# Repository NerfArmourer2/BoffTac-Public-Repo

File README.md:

All content is CC0 or Public Domain. These works can be used for any purpose, commerical or otherwise, with the need for permission. I would appreciate attribution where appropriate, however. :)

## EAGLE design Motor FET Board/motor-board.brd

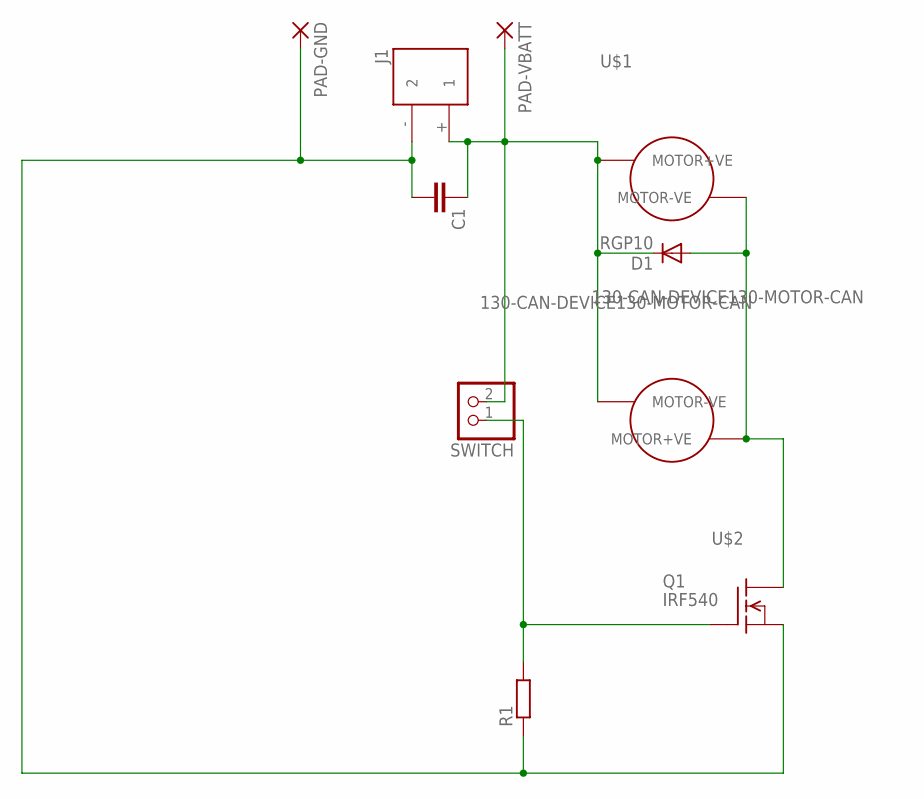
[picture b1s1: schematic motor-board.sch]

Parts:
C1: C-EU050-024X044; C050-024X044
D1: RGP10; DO41-10
J1: XT60_FEMALE
PAD-GND: WIREPAD3,81/1,4; 3,81/1,4
PAD-VBATT: WIREPAD3,81/1,4; 3,81/1,4
Q1: IRF540; TO220
R1: R-EU_0309/10; 0309/10
SWITCH: PINHD-1X2; 1X02
U$1, U$2: 130-CAN-DEVICE130-MOTOR-CAN; 130-MOTOR-CAN

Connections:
GND: C1.2, J1.- (2), PAD-GND.1, Q1.3 (S), R1.1
MOTOR-VE: D1.A, Q1.2 (D), U$1.MOTOR-VE, U$2.MOTOR+VE
unnamed: Q1.1 (G), R1.2, SWITCH.1
VBATT: C1.1, D1.C, J1.+ (1), PAD-VBATT.1, SWITCH.2, U$1.MOTOR+VE, U$2.MOTOR-VE

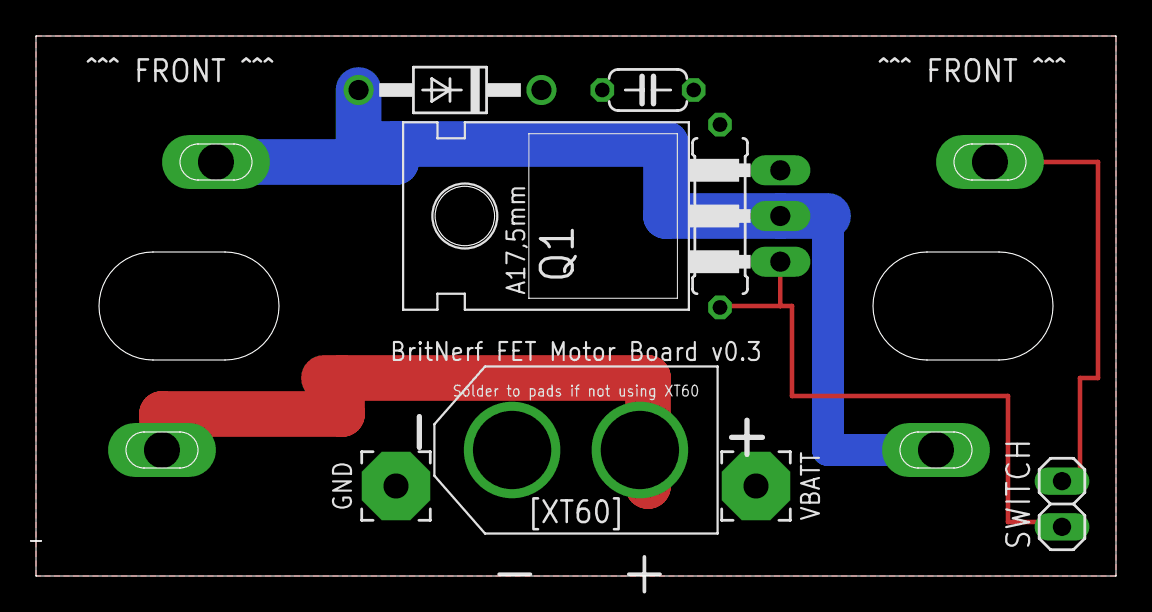
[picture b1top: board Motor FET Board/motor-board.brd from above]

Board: 2 copper layers, 60.0 x 30.0 mm, 10 parts (0 on the bottom side), 4 nets.

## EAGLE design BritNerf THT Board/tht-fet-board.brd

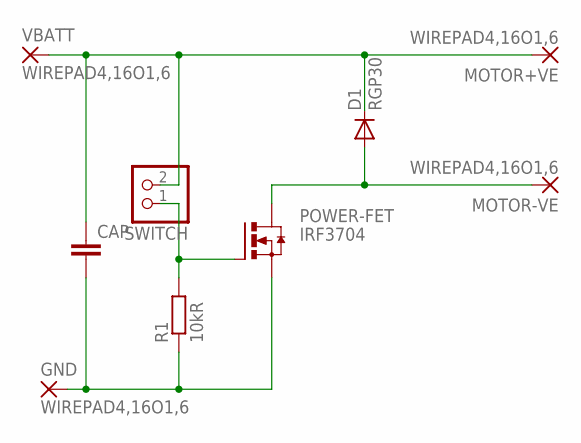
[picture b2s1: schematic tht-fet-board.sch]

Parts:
CAP: C-EU025-024X044; C025-024X044
D1: RGP30; DO201-15
GND: WIREPAD4,16O1,6; 4,16O1,6
MOTOR+VE: WIREPAD4,16O1,6; 4,16O1,6
MOTOR-VE: WIREPAD4,16O1,6; 4,16O1,6
POWER-FET: IRF3704; TO220AH
R1: 10kR; 0207/15
SWITCH: PINHD-1X2; 1X02
VBATT: WIREPAD4,16O1,6; 4,16O1,6

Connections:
GATE: POWER-FET.B (G), R1.2, SWITCH.1
GND: CAP.2, GND.1, POWER-FET.E (S), R1.1
MOTOR-VE: D1.A, MOTOR-VE.1, POWER-FET.C (D)
VBATT: CAP.1, D1.C, MOTOR+VE.1, SWITCH.2, VBATT.1

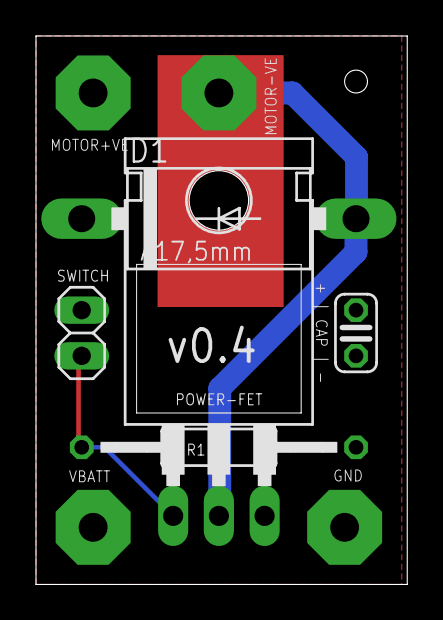
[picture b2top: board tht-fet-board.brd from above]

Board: 2 copper layers, 20.6 x 30.5 mm, 9 parts (0 on the bottom side), 4 nets.

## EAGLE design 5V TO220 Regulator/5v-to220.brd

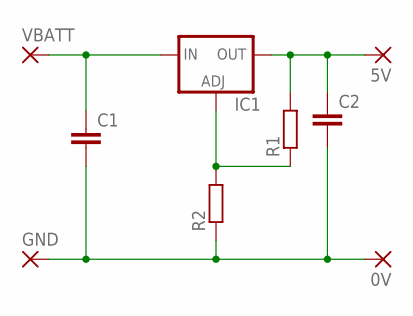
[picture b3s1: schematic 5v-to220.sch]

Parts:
0V, 5V: WIREPAD4,16O1,6; 4,16O1,6
C1, C2: C-EU050-024X044; C050-024X044
GND: WIREPAD4,16O1,6; 4,16O1,6
IC1: LM138-TL; TO220L1
R1, R2: R-EU_0207/10; 0207/10
VBATT: WIREPAD4,16O1,6; 4,16O1,6

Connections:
5V: 5V.1, C2.1, IC1.2 (OUT), R1.2
ADJ: IC1.1 (ADJ), R1.1, R2.2
GND: 0V.1, C1.2, C2.2, GND.1, R2.1
VBATT: C1.1, IC1.3 (IN), VBATT.1

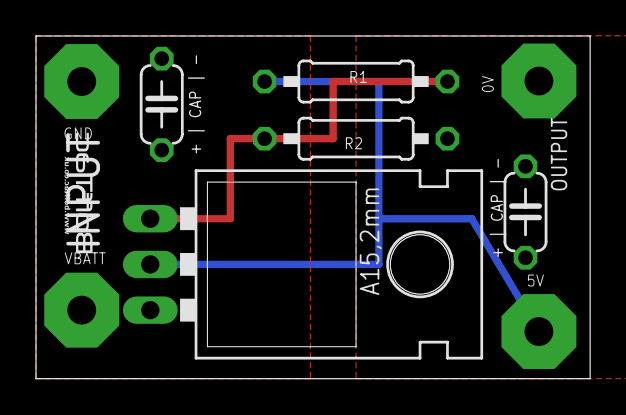
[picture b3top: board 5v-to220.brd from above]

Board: 2 copper layers, 30.8 x 19.0 mm, 9 parts (0 on the bottom side), 4 nets.

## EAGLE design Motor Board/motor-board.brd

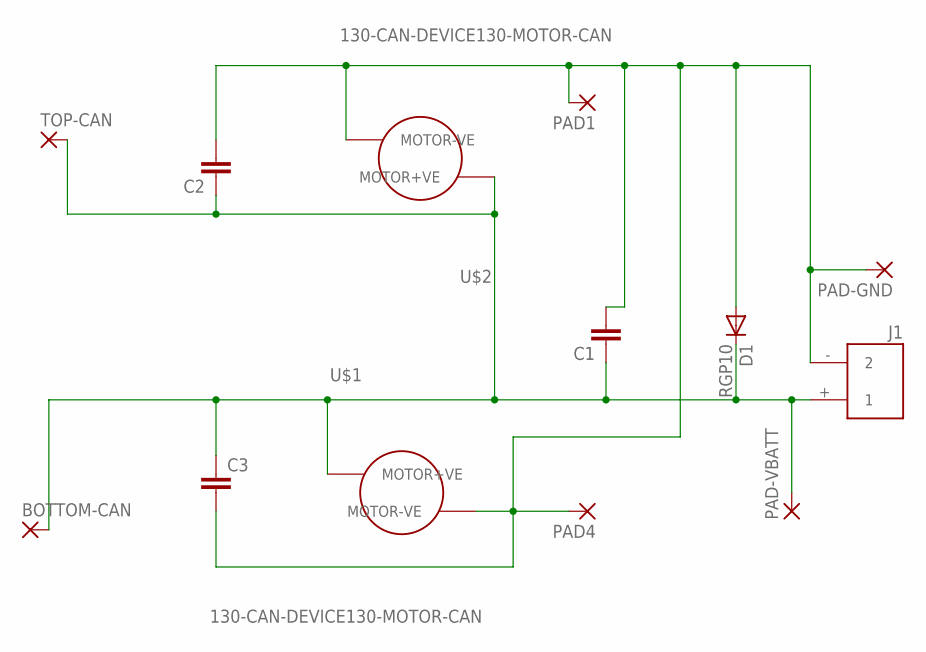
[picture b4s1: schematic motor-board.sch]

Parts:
BOTTOM-CAN: WIREPADSMD1,27-254; SMD1,27-2,54
C1, C2, C3: C-EU050-024X044; C050-024X044
D1: RGP10; DO41-10
J1: XT60_FEMALE
PAD1, PAD4: WIREPADSMD1,27-254; SMD1,27-2,54
PAD-GND: WIREPAD3,81/1,4; 3,81/1,4
PAD-VBATT: WIREPAD3,81/1,4; 3,81/1,4
TOP-CAN: WIREPADSMD1,27-254; SMD1,27-2,54
U$1, U$2: 130-CAN-DEVICE130-MOTOR-CAN; 130-MOTOR-CAN

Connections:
GND: C1.2, C2.2, C3.2, D1.A, J1.- (2), PAD1.1, PAD4.1, PAD-GND.1, U$1.MOTOR-VE, U$2.MOTOR-VE
VBATT: BOTTOM-CAN.1, C1.1, C2.1, C3.1, D1.C, J1.+ (1), PAD-VBATT.1, TOP-CAN.1, U$1.MOTOR+VE, U$2.MOTOR+VE

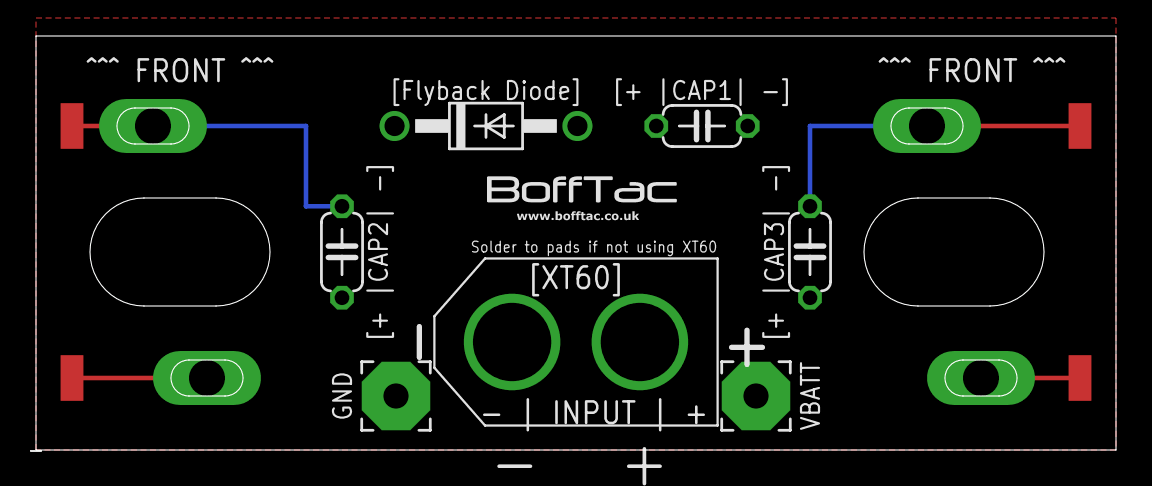
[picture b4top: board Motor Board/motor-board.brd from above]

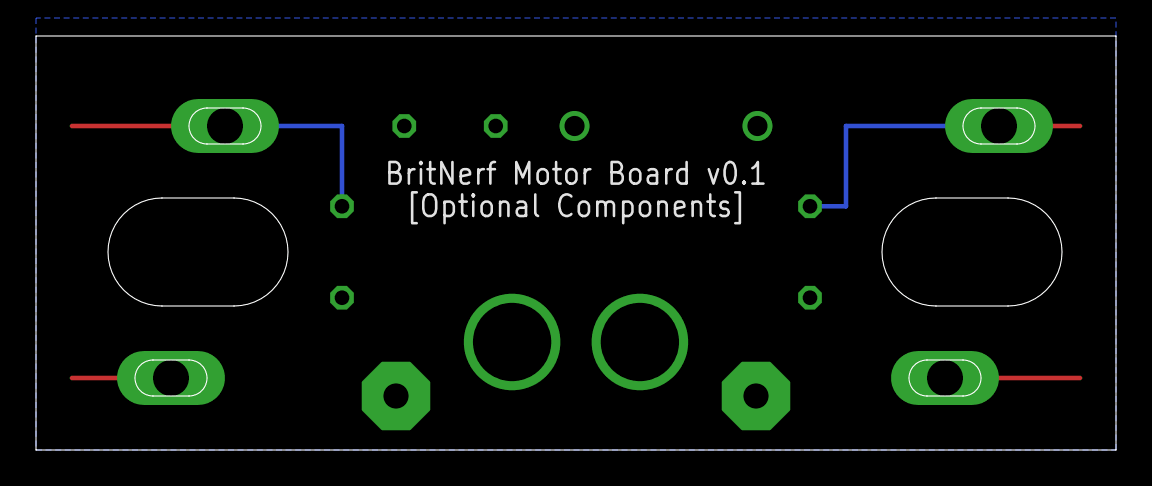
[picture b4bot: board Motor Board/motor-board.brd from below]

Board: 2 copper layers, 60.0 x 23.0 mm, 13 parts (2 on the bottom side), 2 nets.

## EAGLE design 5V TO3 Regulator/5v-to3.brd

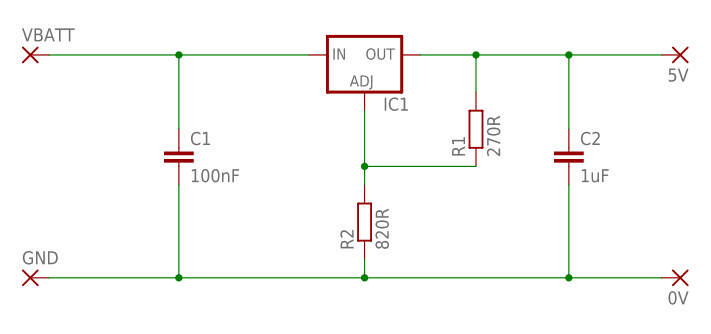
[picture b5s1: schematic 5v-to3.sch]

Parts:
0V, 5V: WIREPAD4,16O1,6; 4,16O1,6
C1: 100nF; C050-024X044
C2: 1uF; C050-024X044
GND: WIREPAD4,16O1,6; 4,16O1,6
IC1: LM138-TO3; TO3-K02
R1: 270R; 0207/7
R2: 820R; 0207/7
VBATT: WIREPAD4,16O1,6; 4,16O1,6

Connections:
5V: 5V.1, C2.1, IC1.3 (OUT), R1.2
ADJ: IC1.2 (ADJ), R1.1, R2.2
GND: 0V.1, C1.2, C2.2, GND.1, R2.1
VBATT: C1.1, IC1.1 (IN), VBATT.1

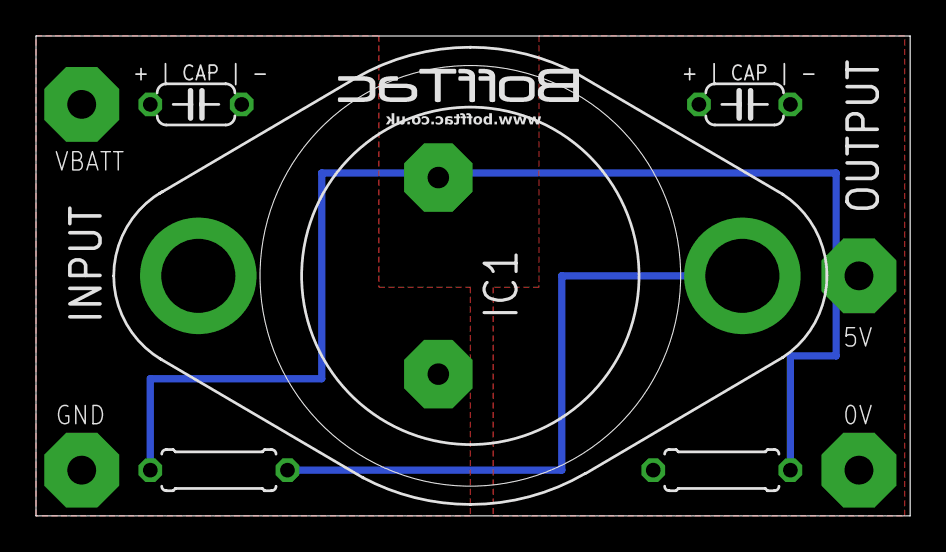
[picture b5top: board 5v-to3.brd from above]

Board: 2 copper layers, 48.6 x 26.7 mm, 9 parts (0 on the bottom side), 4 nets.

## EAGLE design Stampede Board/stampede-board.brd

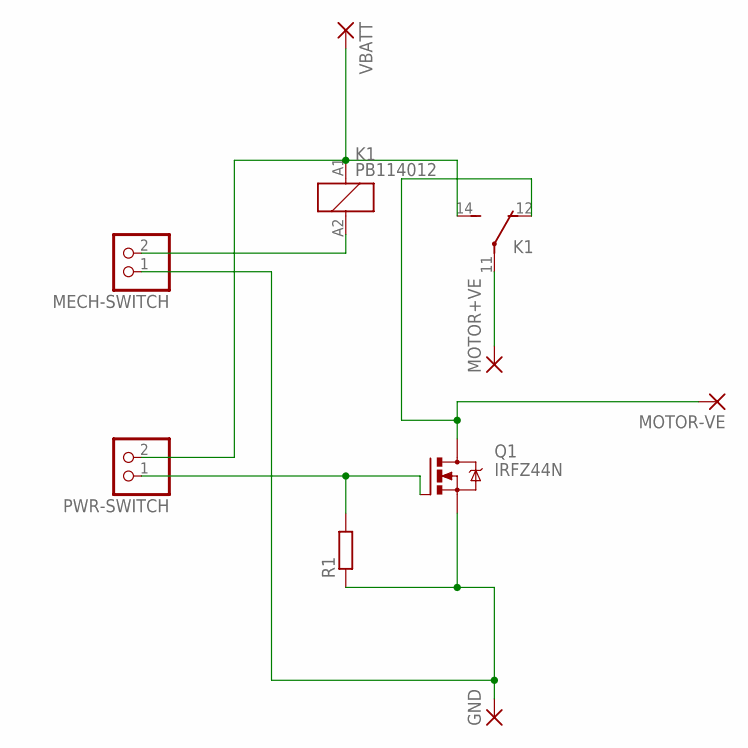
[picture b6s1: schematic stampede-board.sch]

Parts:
GND: WIREPAD3,17/1,3; 3,17/1,3
K1: PB114012; PB
MECH-SWITCH: PINHD-1X2; 1X02
MOTOR+VE: WIREPAD3,17/1,3; 3,17/1,3
MOTOR-VE: WIREPAD3,17/1,3; 3,17/1,3
PWR-SWITCH: PINHD-1X2; 1X02
Q1: IRFZ44N; TO220BV
R1: R-EU_0207/7; 0207/7
VBATT: WIREPAD3,17/1,3; 3,17/1,3

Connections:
GATE: PWR-SWITCH.1, Q1.G, R1.2
GND: GND.1, MECH-SWITCH.1, Q1.S, R1.1
MOTOR+VE: K1.11, MOTOR+VE.1
MOTOR-VE: K1.12 (O), MOTOR-VE.1, Q1.D
unnamed: K1.A2 (2), MECH-SWITCH.2
VBATT: K1.14 (S), K1.A1 (1), PWR-SWITCH.2, VBATT.1

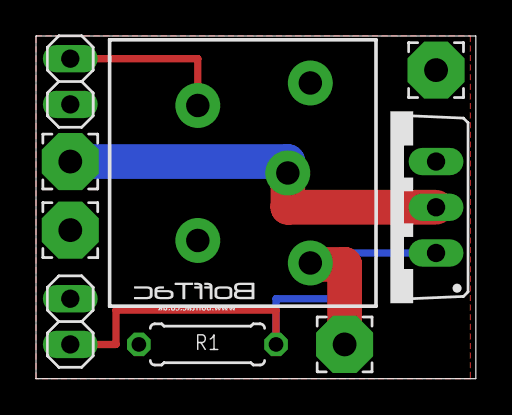
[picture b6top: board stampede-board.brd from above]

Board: 2 copper layers, 24.4 x 19.0 mm, 9 parts (0 on the bottom side), 6 nets.

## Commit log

2019-02-19 Initial commit
    Pushed all the original files to the Repo
2019-02-19 Quality of Life Update
    1: Labelled capacitor polarities on regulator boards
    2: Labelled input and output edges on the same
    3: Ran CAM processor for all changes and added them to a manufacturer friendly .zip file
2019-02-19 Motor Board Push
    Added a PCB mounting board for motors including EMF suppression and optional flyback diode.
    Also added a motor footprint library that needs testing.
2019-02-19 Stampede Board Gerber Files
    Processed Gerber files for Stampede board
2019-03-11 Board Update
    Redefined 130 motor can and updated board to add solder pads if not using XT60 connectors
2019-03-14 TO220 Reg Update
    > Adjusted position of output solder pads to improve cable layouts
    > Improved silkscreen labelling
    > Rotated caps so +ve and -ve are aligned on all caps
2019-03-14 Motor Board Update
    > Updated silk screen on motor board to reflect version number
    > Improved on board for motor terminals
2019-03-27 ZIP Files Now Idiot Proof
    Made which files to send to JLC idiot proof.
2019-04-21 Spacing Update
    Updated the motor terminal spacing on the EAGLE files in order to hopefully get it right the third time.
2019-04-21 ZIP File Update
    Updated version number and updated the Zip folder to contain the latest files for fowarding to JLC or other fab houses.
2019-05-02 MOSFET Board Update
    MOSFET Board added to the repo, free for personal use. Updates in this version include a large solder pad behind the FET tab.
2019-05-24 Motor Board Update
    16mm Gap and some other changes
2019-08-07 FET Tab Bug Fix
    Created an open copper space to reduce the need for briding tab to Motor -ve hole
2019-09-26 August 26th Update
    > Consolidated Gerber files for FET and Motor boards
2019-09-26 Motor FET Board 0.1
    Addition of Gerber files for Motor FET board v0.1
2019-09-26 September 26th Update
    > Confirmed bare copper pour behind FETs on standard FET board and on Motor FET Board
2020-12-15 Update README.md
    License changes.
